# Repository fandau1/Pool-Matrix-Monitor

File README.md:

# Pool-Matrix-Monitor

**Simple arduino pool clock with sensors**

Pool-Matrix-Monitor is pool clock with temperature, ph sensor and all this data send to ThingSpeak, or GET to server.

# Main Features
  * [x] Matrix display in cycle(TIME,"Outsite",OUTSITE_TEMPERATURE,"Pool",POOL_TEMPERATURE,"PH sensor", POOL_PH)
  * [x] Measurement of Sensors light, temperature, ph
  * [x] Auto detection connected sensors
  * [x] Auto correct summer and standart time (DST correct)

# How to use?
  **1.** Choose Optimal Board version. Project is saved in **__NAME_OF_BOARD__/...** (example **PoolMatrixNano/...**)  
  **2.** Create circuit or pcb  
  **3.** Upload Arduino Software with Arduino IDE  
  **4.** Put sensors in conectors and you can put in box  

  **[Full Tutorial in CZ language here](https://github.com/fandau1/Pool-Matrix-Monitor/blob/master/TutorialCZ.md)**

# Boards Versions
I have prepering more version of this project so you can choose which is best for you.

|  Boards Versions  | MCU | transfer type pool sensor | SW release | HW release |  Price  |
| :--------: |:---:| :-----------------------: | :--------: | :--------: | :-----------------: |
| [PoolMatrixNano](#poolmatrixnano) | Arduino nano | cable | PMN-v1.0 | PMN-v1.1H | ~13$ |
| PoolMatrixNanoEth | Arduino nano | cable | Not realesed | Not realesed |  |
| PoolMatrixESP32 | ESP32 | cable OR WIFI | Not realesed | Not realesed |  |
| PoolMatrixESP8266 | ESP8266 | cable OR WIFI | Not realesed | Not realesed | |

**for more info with tutorial go to section [All Boards list](boards.md)**

## PoolMatrixNano [[Full version](boards.md#poolmatrixnano)]
**Offline board arduino nano mcu with rtc, matrix display and sensors. Simple cheap and easy for home pool.**

**Basic**
  * Arduino nano
  * DS3231
  * MAX7219 Matrix LED Display Module 4-v-1
  * some resistors

**Optional**
  * DS18B20 *- temperature sensor*
  * Photo Resistor
  * PH sensor PH-4502C

# PCB
  I designed PCB oneside only with some proclaim wires :). So, you can easily create in home or you can solder on prototype pcb. PCB is saved in **__NAME_OF_BOARD__/pcb/** you can choose more version(no ethernet, etc.).

  **PS: In this time you can choose only PoolMatrixNano**

# Installation
 * Download below library and upload code with Arduino IDE to arduino nano. Code is saved in **__NAME_OF_BOARD__/src/** you can choose more version(no ethernet, etc.).

 **In MD_Parola library you must to disable all advance function for a smaller size.**

 **PS: In this time you can choose only PoolMatrixNano**

**Library**
  * [MD_MAX72xx](https://github.com/MajicDesigns/MD_MAX72XX) - *from MajicDesigns*
  * [RTClib](https://github.com/adafruit/RTClib) - *from adafruit*
  * [DallasTemperature](https://github.com/milesburton/Arduino-Temperature-Control-Library) - *from milesburton*
  * [Ethernet2](https://github.com/adafruit/Ethernet2) - *from adafruit*
  * [DST_RTC](https://github.com/andydoro/DST_RTC) - *from andydoro*  

## Planned Features
  * [ ] send data to database (MYSQL), ThingSpeak
  * [ ] ESP8266/ESP32 version
  * [x] NTP synchronize time

## Support
Project is supported if you have any problem contact me. Please give me a :star: if you like my project. If you have any problem feel free and contact me.

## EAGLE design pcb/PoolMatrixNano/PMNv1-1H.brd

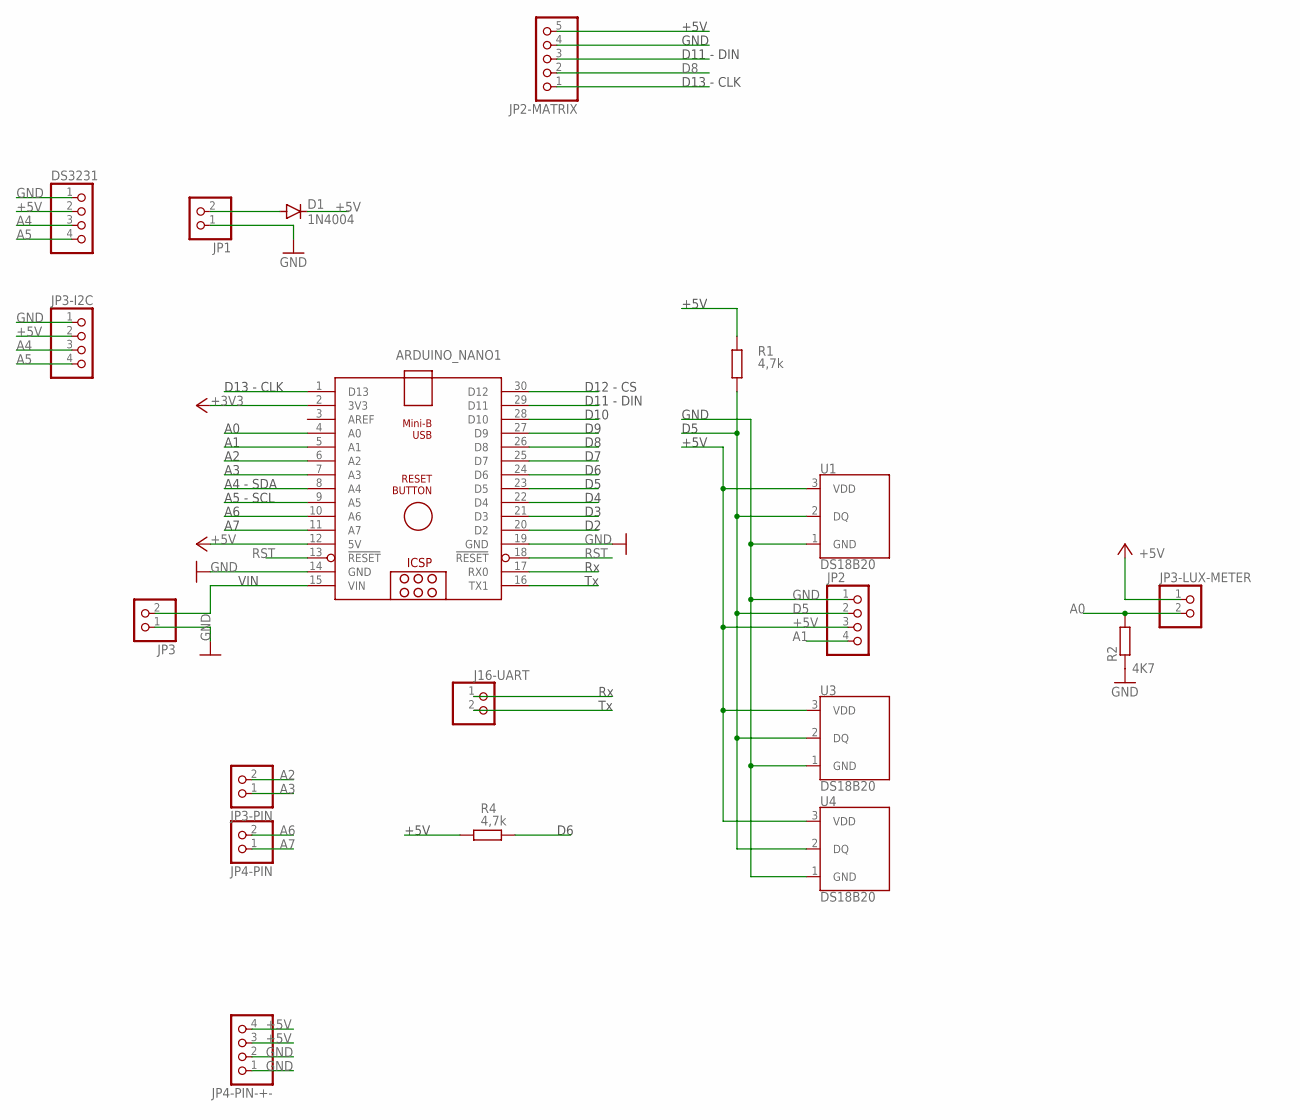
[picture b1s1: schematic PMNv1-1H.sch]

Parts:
ARDUINO_NANO1: ARDUINO_NANO
D1: 1N4004; DO41-10
DS3231: PINHD-1X4; 1X04
J16-UART: PINHD-1X2; 1X02
JP1, JP3, JP3-LUX-METER, JP3-PIN, JP4-PIN: PINHD-1X2; 1X02
JP2, JP3-I2C, JP4-PIN-+-: PINHD-1X4; 1X04
JP2-MATRIX: PINHD-1X5; 1X05
R1, R4: 4,7k; 0204/7
R2: 4K7; 0207/10
U1, U3, U4: DS18B20; TO-92-AMMO

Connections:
+3V3: ARDUINO_NANO1.2 (3V3)
+5V: ARDUINO_NANO1.12 (5V), D1.C, DS3231.2, JP2.3, JP2-MATRIX.5, JP3-I2C.2, JP3-LUX-METER.1, JP4-PIN-+-.3, JP4-PIN-+-.4, R1.1, R4.1, U1.3 (VDD), U3.3 (VDD), U4.3 (VDD)
A0: ARDUINO_NANO1.4 (A0), JP3-LUX-METER.2, R2.2
A1: ARDUINO_NANO1.5 (A1), JP2.4
A2: ARDUINO_NANO1.6 (A2), JP3-PIN.2
A3: ARDUINO_NANO1.7 (A3), JP3-PIN.1
A4: ARDUINO_NANO1.8 (A4), DS3231.3, JP3-I2C.3
A5: ARDUINO_NANO1.9 (A5), DS3231.4, JP3-I2C.4
A6: ARDUINO_NANO1.10 (A6), JP4-PIN.2
A7: ARDUINO_NANO1.11 (A7), JP4-PIN.1
D2: ARDUINO_NANO1.20 (D2)
D3: ARDUINO_NANO1.21 (D3)
D4: ARDUINO_NANO1.22 (D4)
D5: ARDUINO_NANO1.23 (D5), JP2.2, R1.2, U1.2 (DQ), U3.2 (DQ), U4.2 (DQ)
D6: ARDUINO_NANO1.24 (D6), R4.2
D7: ARDUINO_NANO1.25 (D7)
D8: ARDUINO_NANO1.26 (D8), JP2-MATRIX.2
D9: ARDUINO_NANO1.27 (D9)
D10: ARDUINO_NANO1.28 (D10)
D11: ARDUINO_NANO1.29 (D11), JP2-MATRIX.3
D12: ARDUINO_NANO1.30 (D12)
D13: ARDUINO_NANO1.1 (D13), JP2-MATRIX.1
GND: ARDUINO_NANO1.14 (GND), ARDUINO_NANO1.19 (GND), DS3231.1, JP1.1, JP2.1, JP2-MATRIX.4, JP3.1, JP3-I2C.1, JP4-PIN-+-.1, JP4-PIN-+-.2, R2.1, U1.1 (GND), U3.1 (GND), U4.1 (GND)
unnamed: D1.A, JP1.2
RST: ARDUINO_NANO1.13 (!RESET), ARDUINO_NANO1.18 (!RESET)
RX: ARDUINO_NANO1.17 (RX0), J16-UART.1
TX: ARDUINO_NANO1.16 (TX1), J16-UART.2
VIN: ARDUINO_NANO1.15 (VIN), JP3.2

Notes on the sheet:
A4 - SDA
A5 - SCL
D13 - CLK
GND
+5V
D12 - CS
D11 - DIN
D10
VIN

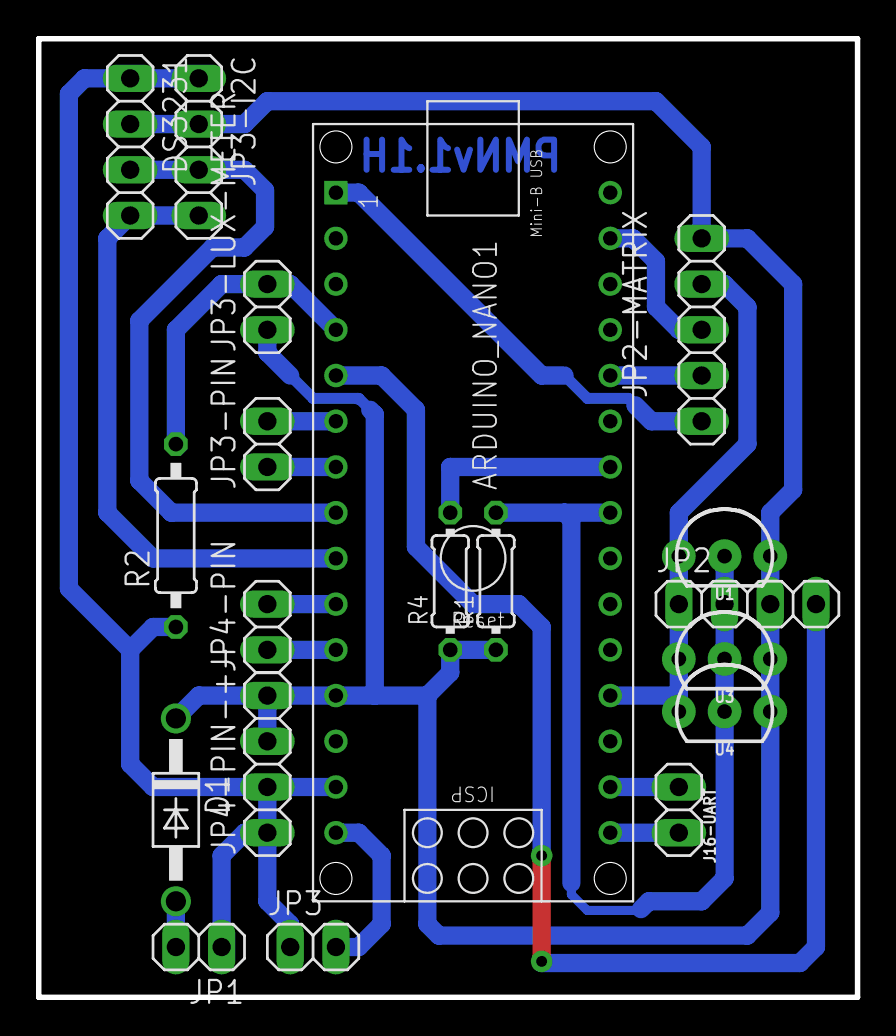
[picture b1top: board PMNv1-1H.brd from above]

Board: 2 copper layers, 45.5 x 53.3 mm, 19 parts (0 on the bottom side), 20 nets.

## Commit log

2020-07-06 Update issue templates
2020-07-07 block pool image
2020-07-07 prototype images
2020-07-07 add images
2020-07-08 v1.0
2020-07-09 v1.0 change
    change structure directory
2020-07-12 update tutorial

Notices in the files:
parts and their libraries:
SparkFun-Sensors: Licensing: Creative Commons ShareAlike 4.0 International - https://creativecommons.org/licenses/by-sa/4.0
